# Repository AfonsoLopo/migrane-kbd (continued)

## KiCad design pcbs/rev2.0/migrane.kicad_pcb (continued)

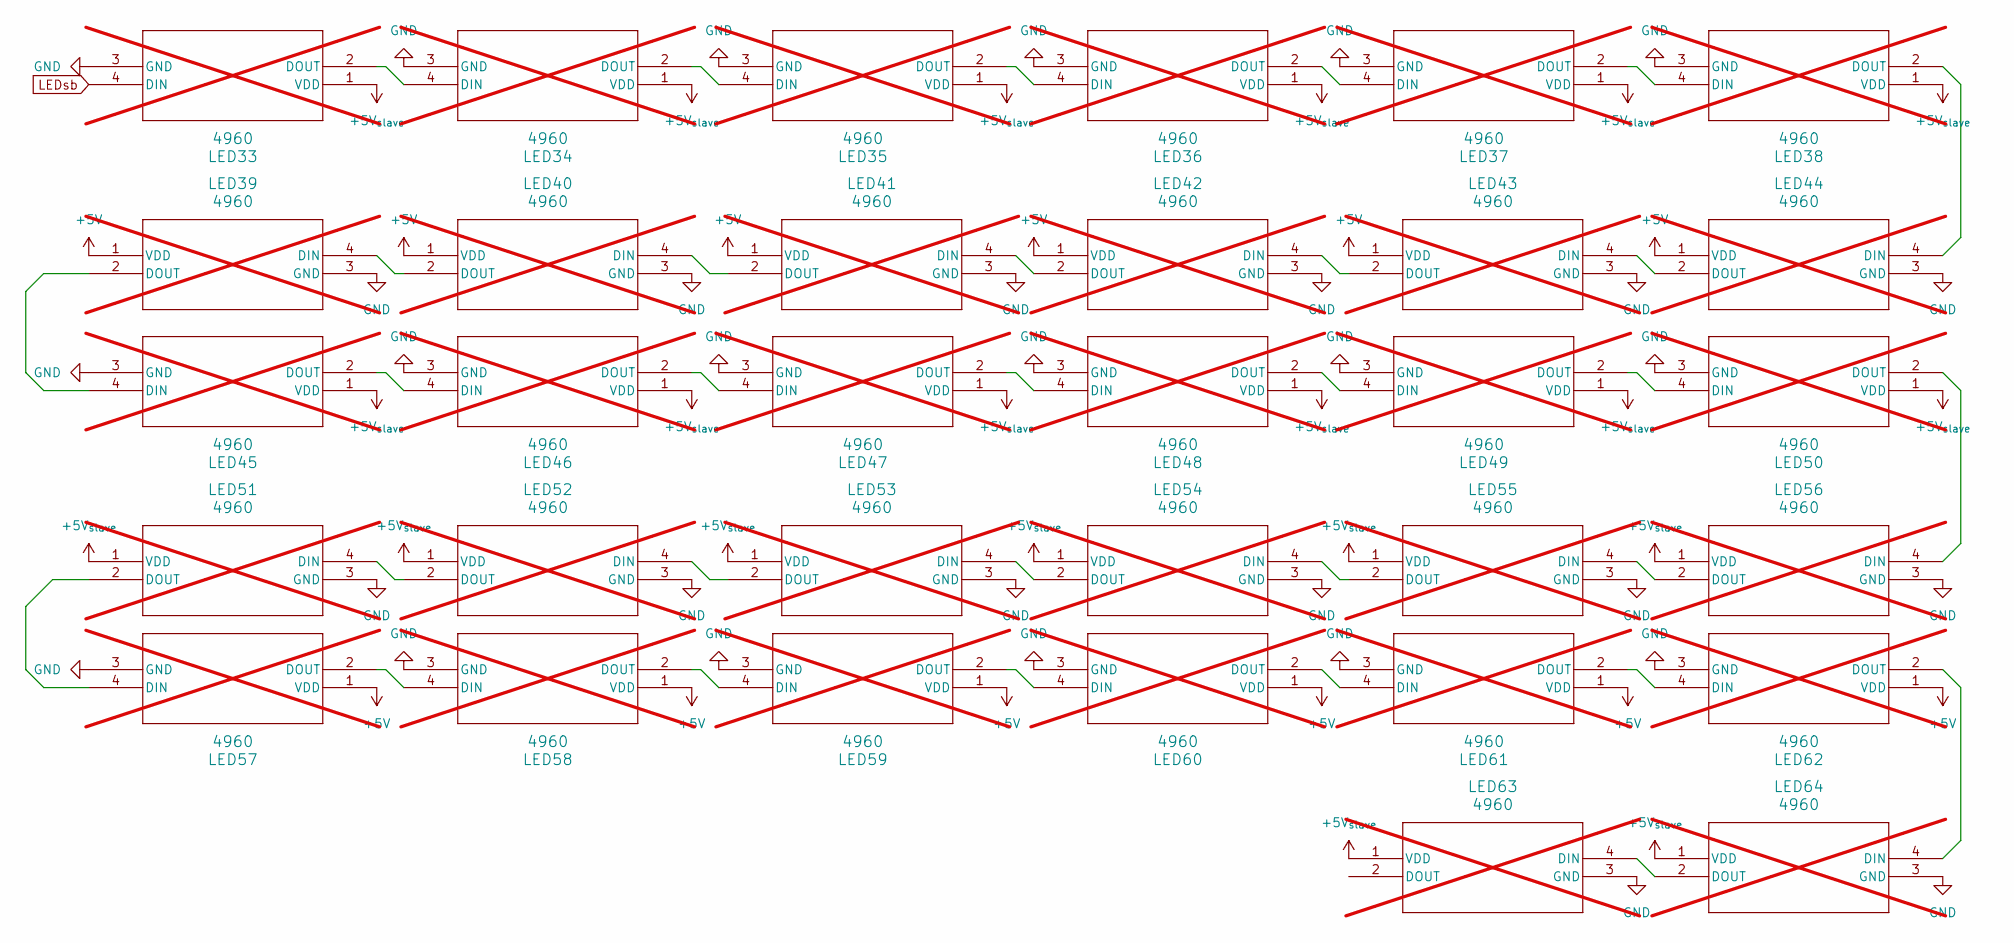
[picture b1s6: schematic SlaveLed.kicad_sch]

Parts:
LED33, LED34, LED35, LED36, LED37, LED38, LED39, LED40, LED41, LED42, LED43, LED44, LED45, LED46, LED47, LED48, LED49, LED50, LED51, LED52, LED53, LED54, LED55, LED56, LED57, LED58, LED59, LED60, LED61, LED62, LED63, LED64: 4960; LED-SMD_L3.2-W2.8-LS5.9_SK6812MINI-E; not fitted

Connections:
+5V: LED39.1 (VDD), LED40.1 (VDD), LED41.1 (VDD), LED42.1 (VDD), LED43.1 (VDD), LED44.1 (VDD), LED57.1 (VDD), LED58.1 (VDD), LED59.1 (VDD), LED60.1 (VDD), LED61.1 (VDD), LED62.1 (VDD); also elsewhere on the board
+5V_{slave}: LED33.1 (VDD), LED34.1 (VDD), LED35.1 (VDD), LED36.1 (VDD), LED37.1 (VDD), LED38.1 (VDD), LED45.1 (VDD), LED46.1 (VDD), LED47.1 (VDD), LED48.1 (VDD), LED49.1 (VDD), LED50.1 (VDD), LED51.1 (VDD), LED52.1 (VDD), LED53.1 (VDD), LED54.1 (VDD), LED55.1 (VDD), LED56.1 (VDD), LED63.1 (VDD), LED64.1 (VDD); also elsewhere on the board
GND: LED33.3 (GND), LED34.3 (GND), LED35.3 (GND), LED36.3 (GND), LED37.3 (GND), LED38.3 (GND), LED39.3 (GND), LED40.3 (GND), LED41.3 (GND), LED42.3 (GND), LED43.3 (GND), LED44.3 (GND), LED45.3 (GND), LED46.3 (GND), LED47.3 (GND), LED48.3 (GND), LED49.3 (GND), LED50.3 (GND), LED51.3 (GND), LED52.3 (GND), LED53.3 (GND), LED54.3 (GND), LED55.3 (GND), LED56.3 (GND), LED57.3 (GND), LED58.3 (GND), LED59.3 (GND), LED60.3 (GND), LED61.3 (GND), LED62.3 (GND), LED63.3 (GND), LED64.3 (GND); also elsewhere on the board
LEDsb: LED33.4 (DIN)
unnamed: LED33.2 (DOUT), LED34.4 (DIN)
unnamed: LED34.2 (DOUT), LED35.4 (DIN)
unnamed: LED35.2 (DOUT), LED36.4 (DIN)
unnamed: LED36.2 (DOUT), LED37.4 (DIN)
unnamed: LED37.2 (DOUT), LED38.4 (DIN)
unnamed: LED38.2 (DOUT), LED44.4 (DIN)
unnamed: LED39.4 (DIN), LED40.2 (DOUT)
unnamed: LED39.2 (DOUT), LED45.4 (DIN)
unnamed: LED40.4 (DIN), LED41.2 (DOUT)
unnamed: LED41.4 (DIN), LED42.2 (DOUT)
unnamed: LED42.4 (DIN), LED43.2 (DOUT)
unnamed: LED43.4 (DIN), LED44.2 (DOUT)
unnamed: LED45.2 (DOUT), LED46.4 (DIN)
unnamed: LED46.2 (DOUT), LED47.4 (DIN)
unnamed: LED47.2 (DOUT), LED48.4 (DIN)
unnamed: LED48.2 (DOUT), LED49.4 (DIN)
unnamed: LED49.2 (DOUT), LED50.4 (DIN)
unnamed: LED50.2 (DOUT), LED56.4 (DIN)
unnamed: LED51.4 (DIN), LED52.2 (DOUT)
unnamed: LED51.2 (DOUT), LED57.4 (DIN)
unnamed: LED52.4 (DIN), LED53.2 (DOUT)
unnamed: LED53.4 (DIN), LED54.2 (DOUT)
unnamed: LED54.4 (DIN), LED55.2 (DOUT)
unnamed: LED55.4 (DIN), LED56.2 (DOUT)
unnamed: LED57.2 (DOUT), LED58.4 (DIN)
unnamed: LED58.2 (DOUT), LED59.4 (DIN)
unnamed: LED59.2 (DOUT), LED60.4 (DIN)
unnamed: LED60.2 (DOUT), LED61.4 (DIN)
unnamed: LED61.2 (DOUT), LED62.4 (DIN)
unnamed: LED62.2 (DOUT), LED64.4 (DIN)
unnamed: LED63.4 (DIN), LED64.2 (DOUT)

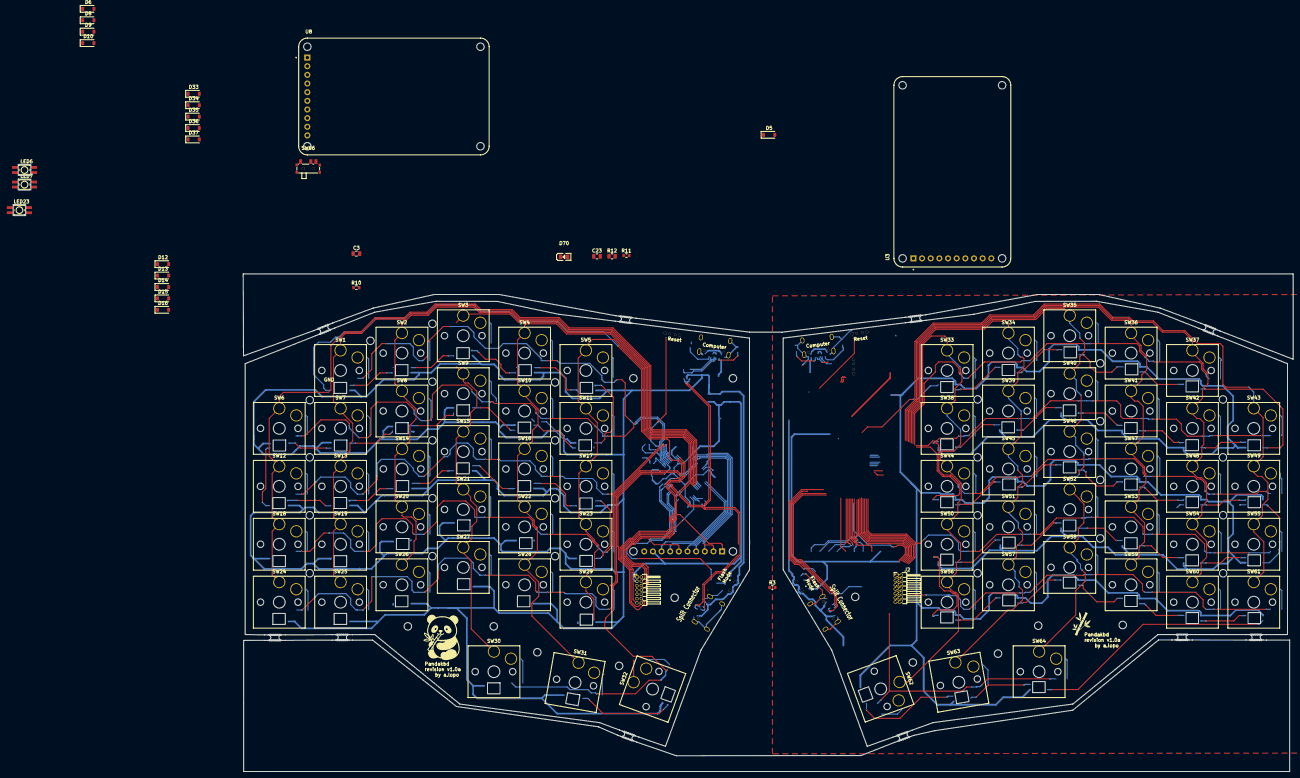
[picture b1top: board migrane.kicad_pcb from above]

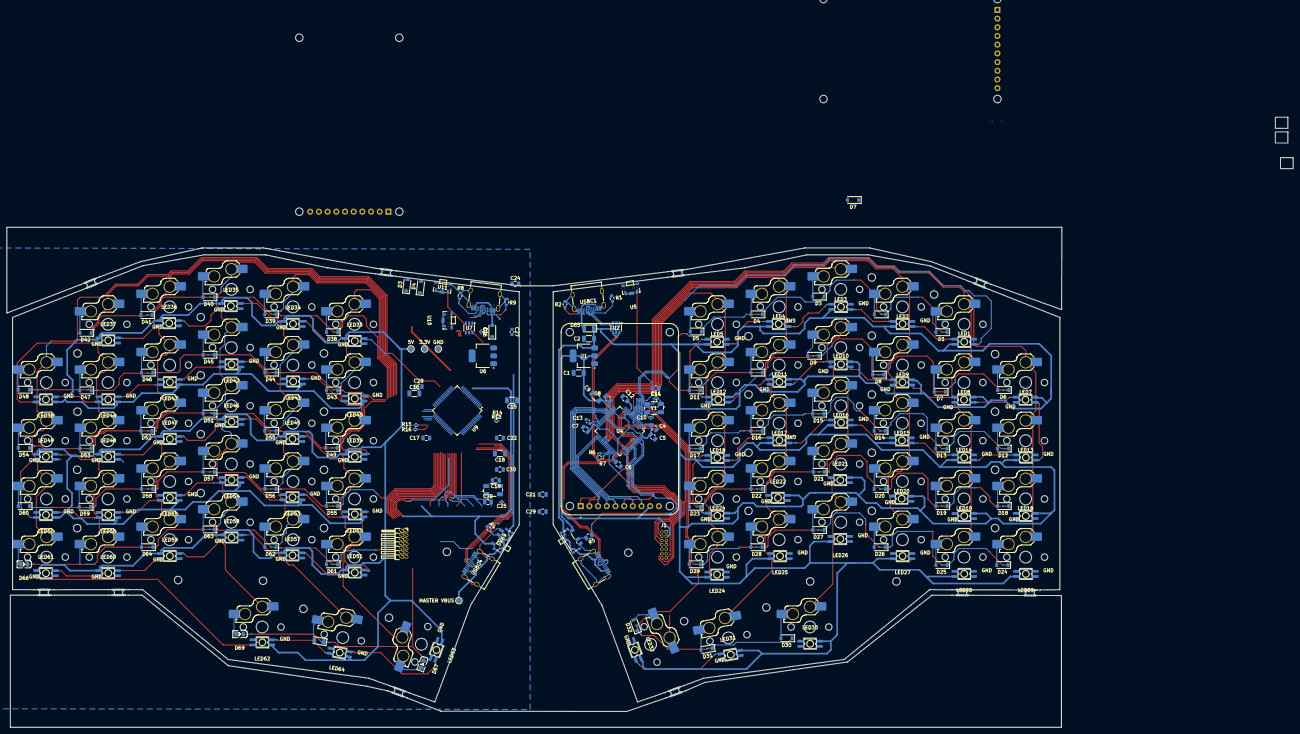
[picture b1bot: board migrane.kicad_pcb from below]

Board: 2 copper layers, 308.1 x 146.0 mm, 290 parts (195 on the bottom side), 214 nets.

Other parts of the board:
3.3V, 5V: +5 V; TestPoint_Pad_D1.5mm
C29, C30: 100nF; C_0805_2012Metric
D1#2, D3#2, D4#2, D5#2, D6#2, D7#2, D8#2, D9#2, D10#2, D12#2, D13#2, D14#2, D15#2, D16#2: 1N4148W; D_SOD-123
G: LOGO; panda
GND: +5 V; TestPoint_Pad_D1.5mm
J1#2: Conn_ST_STDC14; PinHeader_2x07_P1.27mm_Horizontal
LED7#2, LED18#2, LED24#2: SK6812mini-e; LED-SMD_L3.2-W2.8-LS5.9_SK6812MINI-E
MASTER VBUS: +5 V; TestPoint_Pad_D1.5mm
R3: 33Ω; R_0603_1608Metric
R4: 300; R_0603_1608Metric
R15, R16: 22; R_0402_1005Metric
SW69: MK-12C03-G015; SW-SMD_MK-12C03-G015
U3#2: 358; MODULE_358
U11: GT-TC020A-H035-L05; SW-SMD_GT-TC020B-H035-L05

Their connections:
+3.3V: 3.3V.2, C29.1, C30.2, R3.2; also elsewhere on the board
+3.3V_{master}: J1#2.3 (VCC), U3#2.9 (VCC); also elsewhere on the board
+3.3V_{slave}: SW69.1; also elsewhere on the board
+5V: 5V.1, R4.2; also elsewhere on the board
+5V_{master}: LED7#2.1 (VDD), LED18#2.1 (VDD), LED24#2.1 (VDD); also elsewhere on the board
/right/SW_BOOT0b: SW69.2; also elsewhere on the board
CS^{a}: U3#2.5 (TFT_CS); also elsewhere on the board
DataCommand^{a}: U3#2.7 (D/C); also elsewhere on the board
GND: C29.2, C30.1, J1#2.5 (GND), J1#2.7 (GND), LED7#2.3 (GND), LED18#2.3 (GND), LED24#2.3 (GND), SW69.3, U3#2.10 (GND), U11.2, U11.3, U11.4; also elsewhere on the board
LCDReset^{a}: U3#2.8 (RESET); also elsewhere on the board
MISO^{a}: U3#2.2 (MISO); also elsewhere on the board
MOSI^{a}: U3#2.4 (MOSI); also elsewhere on the board
unnamed 44: D1#2.2 (A); also elsewhere on the board
unnamed 46: D3#2.2 (A); also elsewhere on the board
unnamed 47: D4#2.2 (A); also elsewhere on the board
unnamed 48: D5#2.2 (A); also elsewhere on the board
unnamed 49: D6#2.2 (A); also elsewhere on the board
unnamed 50: D7#2.2 (A); also elsewhere on the board
unnamed 51: D8#2.2 (A); also elsewhere on the board
unnamed 52: D9#2.2 (A); also elsewhere on the board
unnamed 53: D10#2.2 (A); also elsewhere on the board
unnamed 55: D12#2.2 (A); also elsewhere on the board
unnamed 56: D13#2.2 (A); also elsewhere on the board
unnamed 57: D14#2.2 (A); also elsewhere on the board
unnamed 58: D15#2.2 (A); also elsewhere on the board
unnamed 59: D16#2.2 (A); also elsewhere on the board
unnamed 117: LED7#2.4 (DIN); also elsewhere on the board
unnamed 123: LED7#2.2 (DOUT); also elsewhere on the board
unnamed 128: LED18#2.4 (DIN); also elsewhere on the board
unnamed 129: LED18#2.2 (DOUT), LED24#2.4 (DIN); also elsewhere on the board
unnamed 135: LED24#2.2 (DOUT); also elsewhere on the board
unnamed 175: R15.1; also elsewhere on the board
unnamed 176: R16.1; also elsewhere on the board
RESET^{a}: J1#2.12 (~RST); also elsewhere on the board
RESETb: U11.1; also elsewhere on the board
ROW0^{a}: D1#2.1 (K), D3#2.1 (K), D4#2.1 (K), D5#2.1 (K); also elsewhere on the board
ROW1^{a}: D6#2.1 (K), D7#2.1 (K), D8#2.1 (K), D9#2.1 (K), D10#2.1 (K); also elsewhere on the board
ROW2^{a}: D12#2.1 (K), D13#2.1 (K), D14#2.1 (K), D15#2.1 (K), D16#2.1 (K); also elsewhere on the board
SCK^{a}: U3#2.3 (SCK); also elsewhere on the board
SDCS^{a}: U3#2.6 (CARD_CS); also elsewhere on the board
SWCLK^{a}: J1#2.6 (JCLK/SWCLK); also elsewhere on the board
SWDIO^{a}: J1#2.4 (JTMS/SWDIO); also elsewhere on the board
SWO^{a}: J1#2.8 (JTDO/SWO); also elsewhere on the board
ScreenBright^{a}: U3#2.1 (LITE); also elsewhere on the board
UART_RX^{a}: J1#2.13 (VCP_RX); also elsewhere on the board
UART_TX^{a}: J1#2.14 (VCP_TX); also elsewhere on the board

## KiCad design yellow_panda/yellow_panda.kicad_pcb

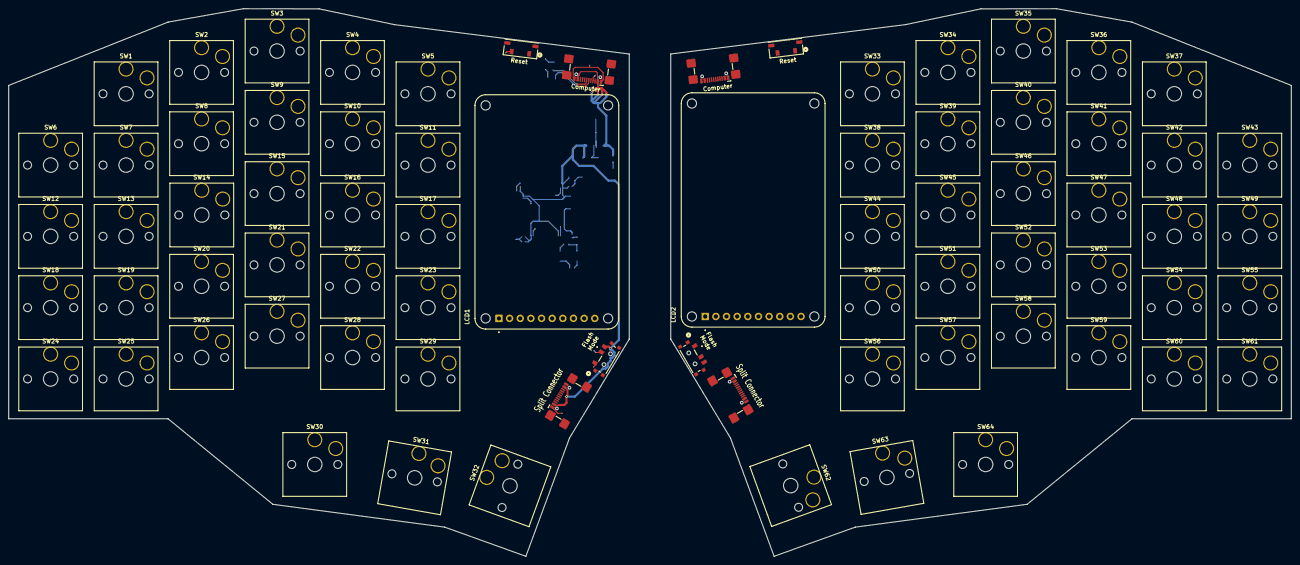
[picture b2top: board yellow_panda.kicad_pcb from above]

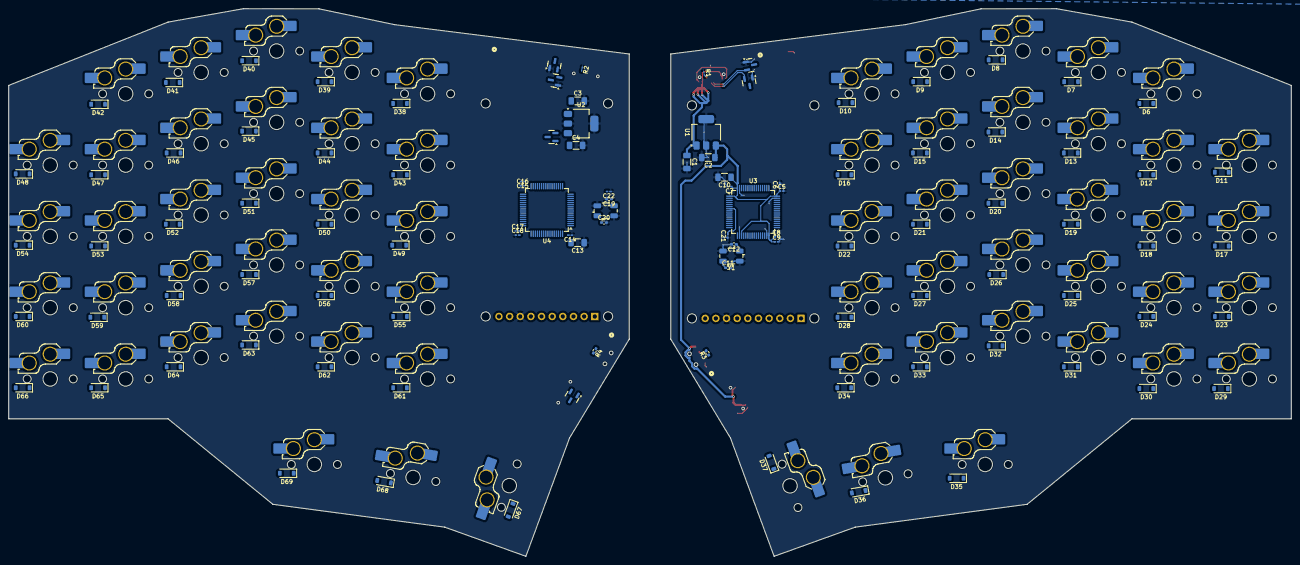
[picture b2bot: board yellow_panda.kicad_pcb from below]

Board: 2 copper layers, 305.9 x 130.6 mm, 176 parts (102 on the bottom side), 109 nets.

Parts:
C1, C2, C3, C4, C10, C13: 10uF; C_1206_3216Metric_Pad1.33x1.80mm_HandSolder
C5, C6, C7, C8, C9, C14, C15, C16, C17, C18, C21, C22: 100nF; C_0201_0603Metric_Pad0.64x0.40mm_HandSolder
C11, C12, C19, C20: 15pF; C_0402_1005Metric_Pad0.74x0.62mm_HandSolder
D1, D70: D_Schottky; D_SOT-23
D2, D3, D4, D5: 5V; D_SOT-23
D6, D7, D8, D9, D10, D11, D12, D13, D14, D15, D16, D17, D18, D19, D20, D21, D22, D23, D24, D25, D26, D27, D28, D29, D30, D31, D32, D33, D34, D35, D36, D37, D38, D39, D40, D41, D42, D43, D44, D45, D46, D47, D48, D49, D50, D51, D52, D53, D54, D55, D56, D57, D58, D59, D60, D61, D62, D63, D64, D65, D66, D67, D68, D69: D_SOD-123
LCD1, LCD2: I2C LCD; MODULE_358
P1, P2: USB_C_Plug_USB2.0; USB_C_Receptacle_GCT_USB4110
P3: Master Connection Plug; USB_C_Receptacle_GCT_USB4110
P4: Slave Connection Plug; USB_C_Receptacle_GCT_USB4110
R1, R2: 5.1kΩ; R_01005_0402Metric_Pad0.57x0.30mm_HandSolder
R3, R4: 10k; R_0402_1005Metric_Pad0.72x0.64mm_HandSolder
SW1, SW2, SW3, SW4, SW5, SW6, SW7, SW8, SW9, SW10, SW11, SW12, SW13, SW14, SW15, SW16, SW17, SW18, SW19, SW20, SW21, SW22, SW23, SW24, SW25, SW26, SW27, SW28, SW29, SW30, SW31, SW33, SW34, SW35, SW36, SW37, SW38, SW39, SW40, SW41, SW42, SW43, SW44, SW45, SW46, SW47, SW48, SW49, SW50, SW51, SW52, SW53, SW54, SW55, SW56, SW57, SW58, SW59, SW60, SW61, SW63, SW64: SW_Hotswap_Kailh_Choc_V1_Plated_1.00u
SW32, SW62: SW_Hotswap_Kailh_Choc_V1_Plated_1.50u
SW65, SW66: SW_SPDT; SLW-66527511-SMT-TR_CUD
SW67, SW68: SW_Push; SW_TL3330_EWI
U1, U2: LT1963AxST-3.3; SOT-223-3_TabPin2
U3, U4: STM32F446RCTx; LQFP-64_10x10mm_P0.5mm
Y1, Y2: 8MHz; Crystal_SMD_Abracon_ABM3B-4Pin_5.0x3.2mm

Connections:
+3.3V: C2.1, C5.1, C6.1, C7.1, C8.1, C9.1, C10.1, C13.2, C14.2, C15.2, C16.2, C17.2, C18.2, D1.1 (K), D70.1 (K), P3.A4 (VBUS), P3.A9 (VBUS), P3.B4 (VBUS), P3.B9 (VBUS), SW65.3 (C), U1.3 (OUT), U3.1 (VBAT), U3.19 (VDD), U3.32 (VDD), U3.48 (VDD), U3.64 (VDD), U4.1 (VBAT), U4.19 (VDD), U4.32 (VDD), U4.48 (VDD), U4.64 (VDD)
+5V: C1.1, C3.1, P1.A4 (VBUS), P1.A9 (VBUS), P1.B4 (VBUS), P1.B9 (VBUS), P2.A4 (VBUS), P2.A9 (VBUS), P2.B4 (VBUS), P2.B9 (VBUS), U1.1 (IN), U2.1 (IN)
/MasterSwitchMatrix/COL0a: SW6.1, SW12.1, SW18.1, SW24.1
/MasterSwitchMatrix/COL1a: SW1.1, SW7.1, SW13.1, SW19.1, SW25.1
/MasterSwitchMatrix/COL2a: SW2.1, SW8.1, SW14.1, SW20.1, SW26.1
/MasterSwitchMatrix/COL3a: SW3.1, SW9.1, SW15.1, SW21.1, SW27.1, SW30.1
/MasterSwitchMatrix/COL4a: SW4.1, SW10.1, SW16.1, SW22.1, SW28.1, SW31.1
/MasterSwitchMatrix/COL5a: SW5.1, SW11.1, SW17.1, SW23.1, SW29.1, SW32.1
/MasterSwitchMatrix/ROW0a: D6.1 (K), D7.1 (K), D8.1 (K), D9.1 (K), D10.1 (K)
/MasterSwitchMatrix/ROW1a: D11.1 (K), D12.1 (K), D13.1 (K), D14.1 (K), D15.1 (K), D16.1 (K)
/MasterSwitchMatrix/ROW2a: D17.1 (K), D18.1 (K), D19.1 (K), D20.1 (K), D21.1 (K), D22.1 (K)
/MasterSwitchMatrix/ROW3a: D23.1 (K), D24.1 (K), D25.1 (K), D26.1 (K), D27.1 (K), D28.1 (K)
/MasterSwitchMatrix/ROW4a: D29.1 (K), D30.1 (K), D31.1 (K), D32.1 (K), D33.1 (K), D34.1 (K)
/MasterSwitchMatrix/ROW6a: D35.1 (K), D36.1 (K), D37.1 (K)
/STM MCUs/BOOT0a: R3.1, U3.60 (BOOT0)
/STM MCUs/BOOT0b: R4.1, U4.60 (BOOT0)
/STM MCUs/OSC INa: C11.1, Y1.3
/STM MCUs/OSC INb: C19.1, Y2.3
/STM MCUs/OSC OUTa: C12.1, Y1.1
/STM MCUs/OSC OUTb: C20.1, Y2.1
/STM MCUs/RESETa: C21.2, SW67.1, U3.7 (NRST)
/STM MCUs/RESETb: C22.2, SW68.1, U4.7 (NRST)
/STM MCUs/SW_BOOT0a: R3.2, SW65.2 (B)
/STM MCUs/SW_BOOT0b: R4.2, SW66.2 (B)
/SlaveSwitchMatrix/COL0b: SW33.1, SW38.1, SW44.1, SW50.1, SW56.1, SW62.1
/SlaveSwitchMatrix/COL1b: SW34.1, SW39.1, SW45.1, SW51.1, SW57.1, SW63.1
/SlaveSwitchMatrix/COL2b: SW35.1, SW40.1, SW46.1, SW52.1, SW58.1, SW64.1
/SlaveSwitchMatrix/COL3b: SW36.1, SW41.1, SW47.1, SW53.1, SW59.1
/SlaveSwitchMatrix/COL4b: SW37.1, SW42.1, SW48.1, SW54.1, SW60.1
/SlaveSwitchMatrix/COL5b: SW43.1, SW49.1, SW55.1, SW61.1
/SlaveSwitchMatrix/ROW0b: D38.1 (K), D39.1 (K), D40.1 (K), D41.1 (K), D42.1 (K)
/SlaveSwitchMatrix/ROW1b: D43.1 (K), D44.1 (K), D45.1 (K), D46.1 (K), D47.1 (K), D48.1 (K)
/SlaveSwitchMatrix/ROW2b: D49.1 (K), D50.1 (K), D51.1 (K), D52.1 (K), D53.1 (K), D54.1 (K)
/SlaveSwitchMatrix/ROW3b: D55.1 (K), D56.1 (K), D57.1 (K), D58.1 (K), D59.1 (K), D60.1 (K)
/SlaveSwitchMatrix/ROW4b: D61.1 (K), D62.1 (K), D63.1 (K), D64.1 (K), D65.1 (K), D66.1 (K)
/SlaveSwitchMatrix/ROW6b: D67.1 (K), D68.1 (K), D69.1 (K)
/USB_Da+: D2.2 (A), P1.A7 (D-)
/USB_Da-: D4.2 (A), P1.A6 (D+)
/USB_Db+: D3.2 (A), P2.A7 (D-)
/USB_Db-: D5.2 (A), P2.A6 (D+)
GND: C1.2, C2.2, C3.2, C4.2, C5.2, C6.2, C7.2, C8.2, C9.2, C10.2, C11.2, C12.2, C13.1, C14.1, C15.1, C16.1, C17.1, C18.1, C19.2, C20.2, C21.1, C22.1, D2.1 (K), D3.1 (K), D4.1 (K), D5.1 (K), LCD1.8 (VSS), LCD2.8 (VSS), P1.A1 (GND), P1.A12 (GND), P1.B1 (GND), P1.B12 (GND), P1.S1 (SHIELD), P2.A1 (GND), P2.A12 (GND), P2.B1 (GND), P2.B12 (GND), P2.S1 (SHIELD), P3.A1 (GND), P3.A12 (GND), P3.B1 (GND), P3.B12 (GND), P3.S1 (SHIELD), P4.A1 (GND), P4.A12 (GND), P4.B1 (GND), P4.B12 (GND), P4.S1 (SHIELD), R1.1, R2.1, SW65.1 (A), SW66.3 (C), SW67.2, SW68.2, U1.2 (GND), U2.2 (GND), U3.18 (VSS), U3.31 (VSS), U3.47 (VSS), U3.63 (VSS), U4.18 (VSS), U4.31 (VSS), U4.47 (VSS), U4.63 (VSS), Y1.2, Y1.4, Y2.2, Y2.4
unnamed: C4.1, D1.2 (A), U2.3 (OUT)
unnamed: D6.2 (A), SW1.2
unnamed: D7.2 (A), SW2.2
unnamed: D8.2 (A), SW3.2
unnamed: D9.2 (A), SW4.2
unnamed: D10.2 (A), SW5.2
unnamed: D11.2 (A), SW6.2
unnamed: D12.2 (A), SW7.2
unnamed: D13.2 (A), SW8.2
unnamed: D14.2 (A), SW9.2
unnamed: D15.2 (A), SW10.2
unnamed: D16.2 (A), SW11.2
unnamed: D17.2 (A), SW12.2
unnamed: D18.2 (A), SW13.2
unnamed: D19.2 (A), SW14.2
unnamed: D20.2 (A), SW15.2
unnamed: D21.2 (A), SW16.2
unnamed: D22.2 (A), SW17.2
unnamed: D23.2 (A), SW18.2
unnamed: D24.2 (A), SW19.2
unnamed: D25.2 (A), SW20.2
unnamed: D26.2 (A), SW21.2
unnamed: D27.2 (A), SW22.2
unnamed: D28.2 (A), SW23.2
unnamed: D29.2 (A), SW24.2
unnamed: D30.2 (A), SW25.2
unnamed: D31.2 (A), SW26.2
unnamed: D32.2 (A), SW27.2
unnamed: D33.2 (A), SW28.2
unnamed: D34.2 (A), SW29.2
unnamed: D35.2 (A), SW30.2
unnamed: D36.2 (A), SW31.2
unnamed: D37.2 (A), SW32.2
unnamed: D38.2 (A), SW33.2
unnamed: D39.2 (A), SW34.2
unnamed: D40.2 (A), SW35.2
unnamed: D41.2 (A), SW36.2
unnamed: D42.2 (A), SW37.2
unnamed: D43.2 (A), SW38.2
unnamed: D44.2 (A), SW39.2
unnamed: D45.2 (A), SW40.2
unnamed: D46.2 (A), SW41.2
unnamed: D47.2 (A), SW42.2
unnamed: D48.2 (A), SW43.2
unnamed: D49.2 (A), SW44.2
unnamed: D50.2 (A), SW45.2
unnamed: D51.2 (A), SW46.2
unnamed: D52.2 (A), SW47.2
unnamed: D53.2 (A), SW48.2
unnamed: D54.2 (A), SW49.2
unnamed: D55.2 (A), SW50.2
unnamed: D56.2 (A), SW51.2
unnamed: D57.2 (A), SW52.2
unnamed: D58.2 (A), SW53.2
unnamed: D59.2 (A), SW54.2
unnamed: D60.2 (A), SW55.2
unnamed: D61.2 (A), SW56.2
unnamed: D62.2 (A), SW57.2
unnamed: D63.2 (A), SW58.2
unnamed: D64.2 (A), SW59.2
unnamed: D65.2 (A), SW60.2
unnamed: D66.2 (A), SW61.2
unnamed: D67.2 (A), SW62.2
unnamed: D68.2 (A), SW63.2
unnamed: D69.2 (A), SW64.2
unnamed: D70.2 (A), P4.A4 (VBUS), P4.A9 (VBUS), P4.B4 (VBUS), P4.B9 (VBUS)
unnamed: P1.A5 (CC), R1.2
unnamed: P2.A5 (CC), R2.2

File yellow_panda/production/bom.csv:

Designator,Footprint,Quantity,Value,LCSC Part #
"_2, ",bf87ff4d-921f-4e46-abc4-457b704bfae1,2,,
"C1, C10, C13, C2, C3, C4",1206,6,10uF,
"C11, C12, C19, C20",0402,4,15pF,
"C14, C15, C16, C17, C18, C21, C22, C23, C24, C5, C6, C7, C8, C9",0201,14,100nF,
"D1, D4",D_SOT-23,2,D_Schottky,
"D10, D11, D12, D13, D14, D15, D16, D17, D18, D19, D20, D21, D22, D23, D24, D25, D26, D27, D28, D29, D30, D31, D32, D33, D34, D35, D36, D37, D38, D39, D40, D41, D42, D43, D44, D45, D46, D47, D48, D49, D50, D51, D52, D53, D54, D55, D56, D57, D58, D59, D6, D60, D61, D62, D63, D64, D65, D66, D67, D68, D69, D7, D8, D9",D_SOD-123,64,~,
"D2, D3",D_SOD-123FL,2,SMF5.0A,C19077497
"J1, J2",PinHeader_2x07_P1.27mm_Horizontal,2,Conn_ST_STDC14,
"LED1, LED10, LED11, LED12, LED13, LED14, LED15, LED16, LED17, LED18, LED19, LED2, LED20, LED21, LED22, LED23, LED24, LED25, LED26, LED27, LED28, LED29, LED3, LED30, LED31, LED32, LED4, LED5, LED6, LED7, LED8, LED9",4960_ADA,32,4960,
"P1, P2",USB_C_Receptacle_GCT_USB4110,2,USB_C_Plug_USB2.0,
P3,USB_C_Receptacle_GCT_USB4110,1,Master Connection Plug,
P4,USB_C_Receptacle_GCT_USB4110,1,Slave Connection Plug,
"R1, R2",01005,2,5.1kΩ,
"R3, R4",0402,2,10k,
"SW1, SW10, SW11, SW12, SW13, SW14, SW15, SW16, SW17, SW18, SW19, SW2, SW20, SW21, SW22, SW23, SW24, SW25, SW26, SW27, SW28, SW29, SW3, SW30, SW31, SW33, SW34, SW35, SW36, SW37, SW38, SW39, SW4, SW40, SW41, SW42, SW43, SW44, SW45, SW46, SW47, SW48, SW49, SW5, SW50, SW51, SW52, SW53, SW54, SW55, SW56, SW57, SW58, SW59, SW6, SW60, SW61, SW63, SW64, SW7, SW8, SW9",SW_Hotswap_Kailh_Choc_V1_Plated_1.00u,62,~,
"SW32, SW62",SW_Hotswap_Kailh_Choc_V1_Plated_1.50u,2,~,
"SW65, SW66",SLW-66527511-SMT-TR_CUD,2,SW_SPDT,
"SW67, SW68",SW_TL3330_EWI,2,SW_Push,
"U1, U2",SOT-223-3_TabPin2,2,LT1963AxST-3.3,
"U3, U4",LQFP-64_10x10mm_P0.5mm,2,STM32F446RCTx,
"U5, U6",SOT-23-6,2,USBLC6-2SC6,
"U7, U8",MODULE_358,2,358,
"Y1, Y2",Crystal_SMD_Abracon_ABM3B-4Pin_5.0x3.2mm,2,8MHz,

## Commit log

2025-09-18 Everything is in place now
    Swap STM MCU, Correct Switches,
    add diodes, caps and resistors
2025-09-18 Added some routing to power lines
2025-09-19 rev0.1a - master half done
2025-09-20 Finished the design
2025-10-06 Update after fabrication
2025-10-09 v0.1b
2025-10-09 Run it through cleanup
2025-10-11 v1.0a
2025-10-11 rename to pandakbd
2025-10-29 rev2
2025-11-01 prepare placing components
2025-11-03 reorganization of the repo and yet another rename
2025-11-04 start with leds
2025-11-05 Finish Layout for Master Half.
    - Unimplemented handedness yet.
    - Rest of the board should be working already
2025-11-06 ongoing work
2025-11-08 gitignore
2025-11-08 rev3.0
2025-11-08 Add Readme
2025-11-08 add codeowners
2025-11-08 Change LDI3.3 LCSC part number to Diotec part
